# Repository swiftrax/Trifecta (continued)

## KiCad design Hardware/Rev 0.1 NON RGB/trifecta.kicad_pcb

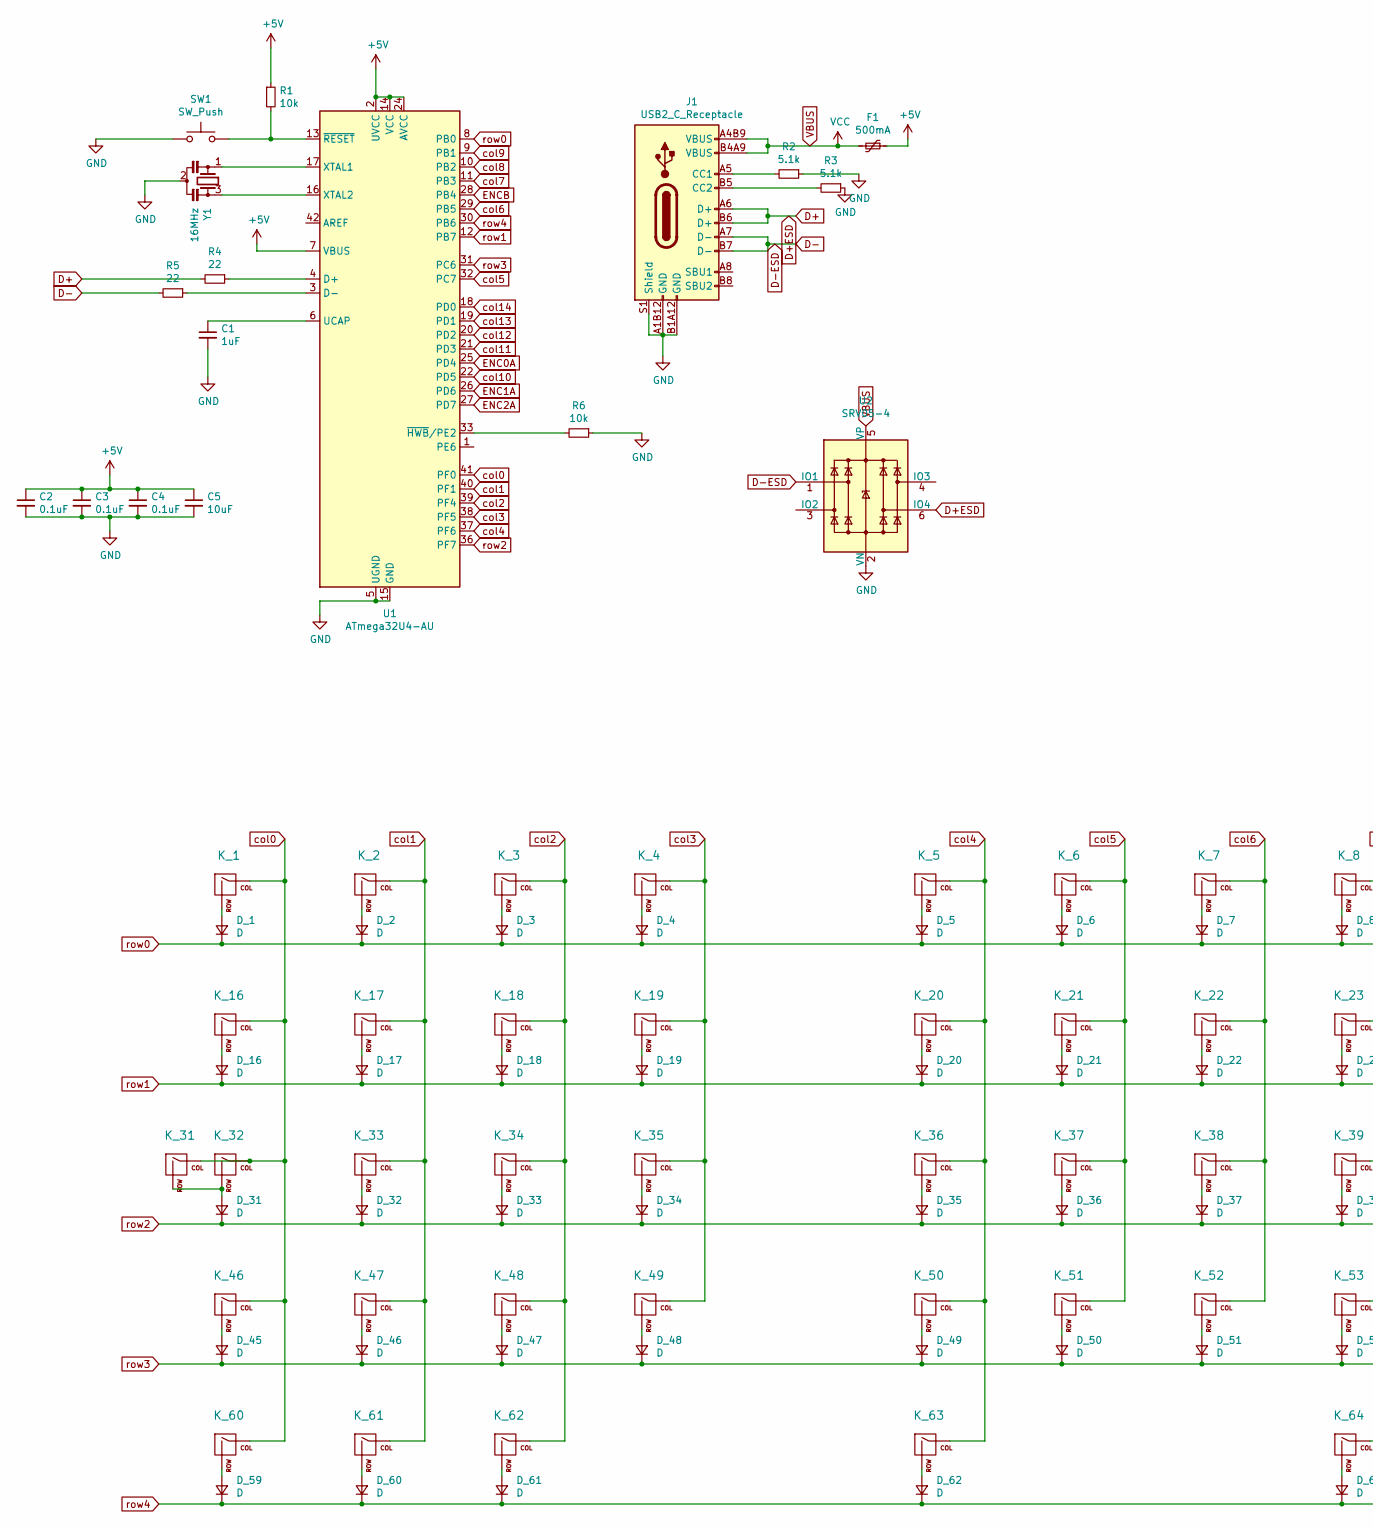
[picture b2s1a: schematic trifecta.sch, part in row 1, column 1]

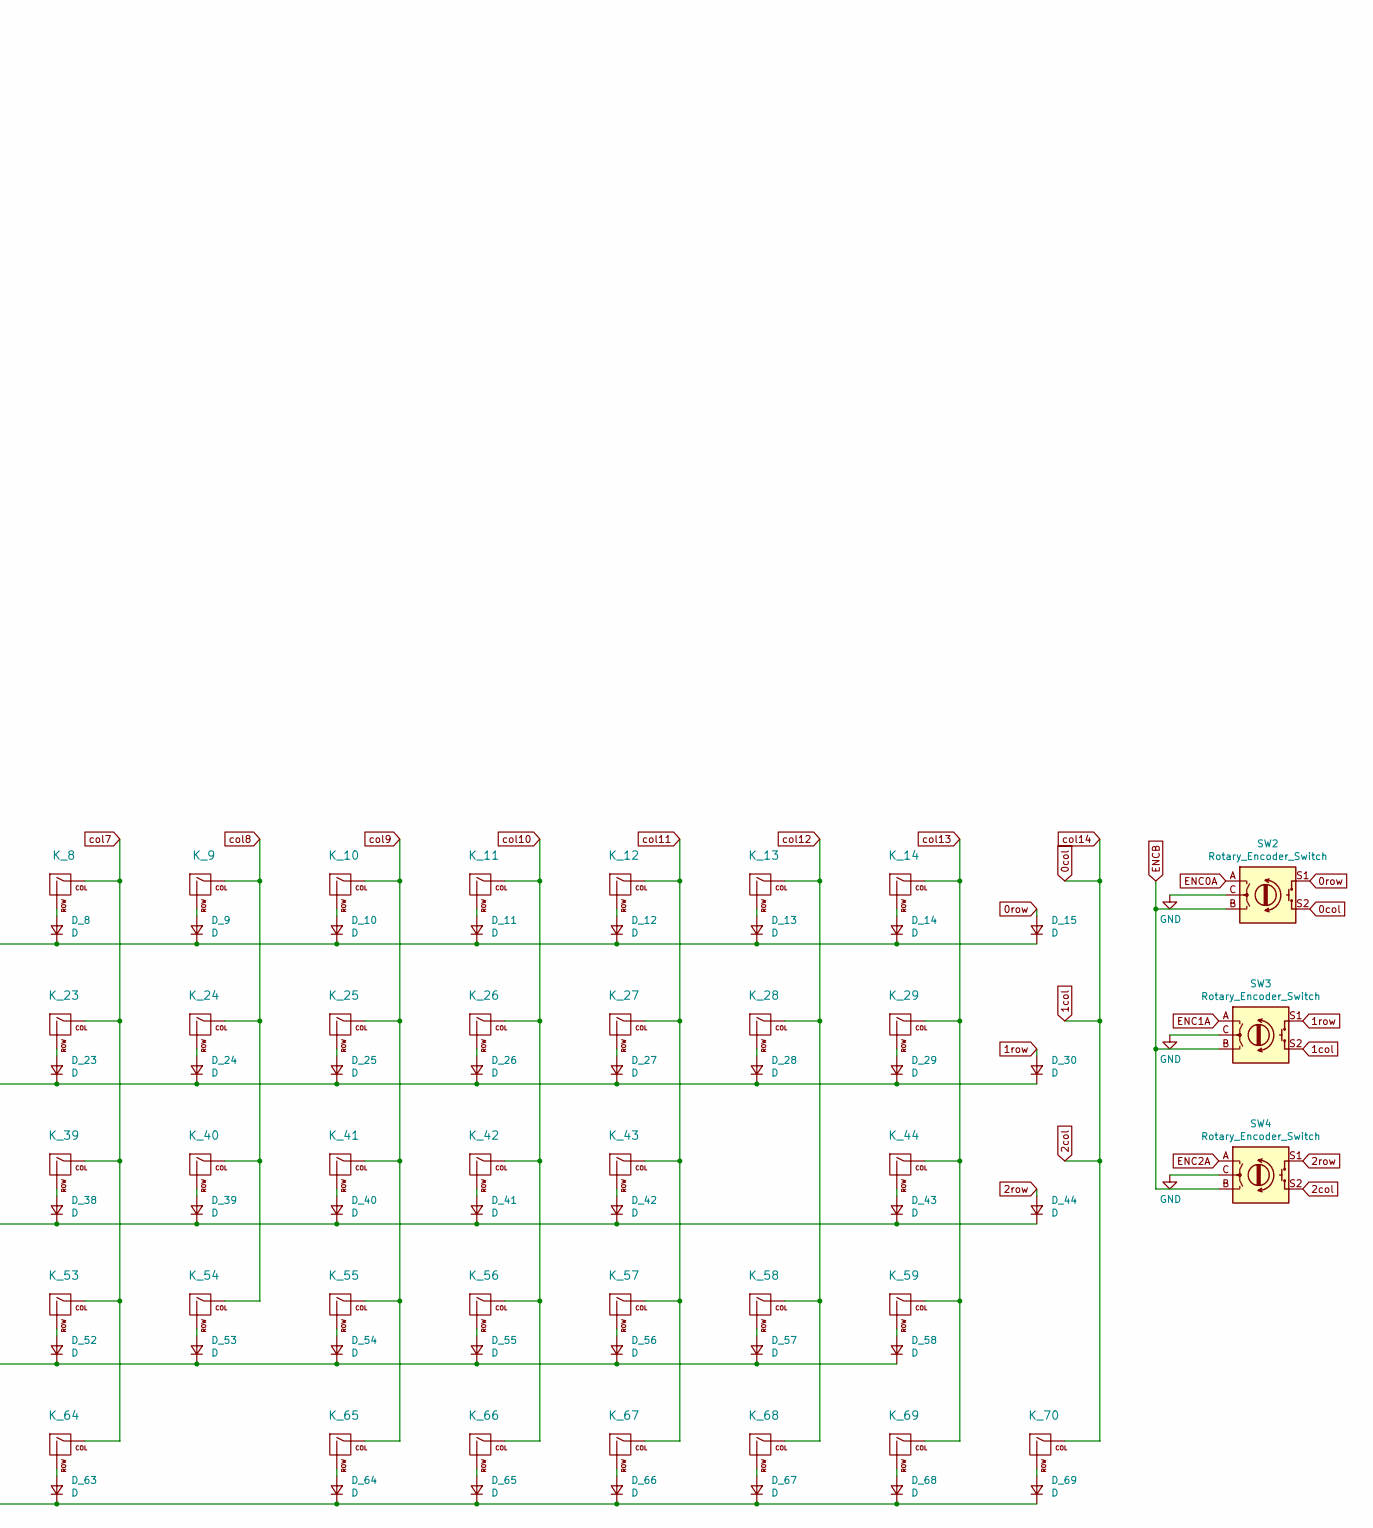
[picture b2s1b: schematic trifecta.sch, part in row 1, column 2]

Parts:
C1: 1uF; C_0805_2012Metric
C2, C3, C4: 0.1uF; C_0805_2012Metric
C5: 10uF; C_0805_2012Metric
D_1, D_2, D_3, D_4, D_5, D_6, D_7, D_8, D_9, D_10, D_11, D_12, D_13, D_14, D_15, D_16, D_17, D_18, D_19, D_20, D_21, D_22, D_23, D_24, D_25, D_26, D_27, D_28, D_29, D_30, D_31, D_32, D_33, D_34, D_35, D_36, D_37, D_38, D_39, D_40, D_41, D_42, D_43, D_44, D_45, D_46, D_47, D_48, D_49, D_50, D_51, D_52, D_53, D_54, D_55, D_56, D_57, D_58, D_59, D_60, D_61, D_62, D_63, D_64, D_65, D_66, D_67, D_68, D_69: D; D_SOD-123
F1: 500mA; Fuse_1206_3216Metric
J1: USB2_C_Receptacle; Mid_Mount-USB_C_HandSoldering
K_1, K_2, K_3, K_4, K_5, K_6, K_7, K_8, K_9, K_10, K_11, K_12, K_13, K_17, K_18, K_19, K_20, K_21, K_22, K_23, K_24, K_25, K_26, K_27, K_28, K_33, K_34, K_35, K_36, K_37, K_38, K_39, K_40, K_41, K_42, K_43, K_47, K_48, K_49, K_50, K_51, K_52, K_53, K_54, K_55, K_56, K_57, K_59, K_68, K_69, K_70: KEYSW; MXOnly-1U-NoLED
K_14: KEYSW; MXOnly-2U-ReversedStabilizers-NoLED
K_16, K_29: KEYSW; MXOnly-1.5U-NoLED
K_31, K_60, K_61, K_62, K_65, K_66, K_67: KEYSW; MXOnly-1.25U-NoLED
K_32, K_58: KEYSW; MXOnly-1.75U-NoLED
K_44, K_46, K_64: KEYSW; MXOnly-2.25U-ReversedStabilizers-NoLED
K_63: KEYSW; MXOnly-2.75U-ReversedStabilizers-NoLED
R1, R6: 10k; R_0805_2012Metric
R2, R3: 5.1k; R_0805_2012Metric
R4, R5: 22; R_0805_2012Metric
SW1: SW_Push; SKQG-1155865
SW2, SW3, SW4: Rotary_Encoder_Switch; RotaryEncoder_EC11
U1: ATmega32U4-AU; TQFP-44_10x10mm_P0.8mm
U2: SRV05-4; SOT-23-6
Y1: 16MHz; Resonator_SMD_muRata_CSTxExxV-3Pin_3.0x1.1mm_HandSoldering_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

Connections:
0col: K_70.1 (COL), SW2.S2, SW3.S2, SW4.S2, U1.18 (PD0)
0row: D_15.2 (A), SW2.S1
1row: D_30.2 (A), SW3.S1
2row: D_44.2 (A), SW4.S1
+5V: C2.1, C3.1, C4.1, C5.1, F1.1, R1.1, U1.2 (UVCC), U1.7 (VBUS), U1.14 (VCC), U1.24 (AVCC), U1.34 (VCC), U1.44 (AVCC)
D+: J1.A6 (D+), J1.B6 (D+), R4.2, U2.6 (IO4)
D-: J1.A7 (D-), J1.B7 (D-), R5.2, U2.1 (IO1)
ENC0A: SW2.A, U1.25 (PD4)
ENC1A: SW3.A, U1.26 (PD6)
ENC2A: SW4.A, U1.27 (PD7)
ENCB: SW2.B, SW3.B, SW4.B, U1.28 (PB4)
GND: C1.2, C2.2, C3.2, C4.2, C5.2, J1.A1B12 (GND), J1.B1A12 (GND), J1.S1 (Shield), R2.1, R3.1, R6.1, SW1.1, SW2.C, SW3.C, SW4.C, U1.5 (UGND), U1.15 (GND), U1.23 (GND), U1.35 (GND), U1.43 (GND), U2.2 (VN), Y1.2
unnamed: C1.1, U1.6 (UCAP)
unnamed: D_1.2 (A), K_1.2 (ROW)
unnamed: D_2.2 (A), K_2.2 (ROW)
unnamed: D_3.2 (A), K_3.2 (ROW)
unnamed: D_4.2 (A), K_4.2 (ROW)
unnamed: D_5.2 (A), K_5.2 (ROW)
unnamed: D_6.2 (A), K_6.2 (ROW)
unnamed: D_7.2 (A), K_7.2 (ROW)
unnamed: D_8.2 (A), K_8.2 (ROW)
unnamed: D_9.2 (A), K_9.2 (ROW)
unnamed: D_10.2 (A), K_10.2 (ROW)
unnamed: D_11.2 (A), K_11.2 (ROW)
unnamed: D_12.2 (A), K_12.2 (ROW)
unnamed: D_13.2 (A), K_13.2 (ROW)
unnamed: D_14.2 (A), K_14.2 (ROW)
unnamed: D_16.2 (A), K_16.2 (ROW)
unnamed: D_17.2 (A), K_17.2 (ROW)
unnamed: D_18.2 (A), K_18.2 (ROW)
unnamed: D_19.2 (A), K_19.2 (ROW)
unnamed: D_20.2 (A), K_20.2 (ROW)
unnamed: D_21.2 (A), K_21.2 (ROW)
unnamed: D_22.2 (A), K_22.2 (ROW)
unnamed: D_23.2 (A), K_23.2 (ROW)
unnamed: D_24.2 (A), K_24.2 (ROW)
unnamed: D_25.2 (A), K_25.2 (ROW)
unnamed: D_26.2 (A), K_26.2 (ROW)
unnamed: D_27.2 (A), K_27.2 (ROW)
unnamed: D_28.2 (A), K_28.2 (ROW)
unnamed: D_29.2 (A), K_29.2 (ROW)
unnamed: D_31.2 (A), K_31.2 (ROW), K_32.2 (ROW)
unnamed: D_32.2 (A), K_33.2 (ROW)
unnamed: D_33.2 (A), K_34.2 (ROW)
unnamed: D_34.2 (A), K_35.2 (ROW)
unnamed: D_35.2 (A), K_36.2 (ROW)
unnamed: D_36.2 (A), K_37.2 (ROW)
unnamed: D_37.2 (A), K_38.2 (ROW)
unnamed: D_38.2 (A), K_39.2 (ROW)
unnamed: D_39.2 (A), K_40.2 (ROW)
unnamed: D_40.2 (A), K_41.2 (ROW)
unnamed: D_41.2 (A), K_42.2 (ROW)
unnamed: D_42.2 (A), K_43.2 (ROW)
unnamed: D_43.2 (A), K_44.2 (ROW)
unnamed: D_45.2 (A), K_46.2 (ROW)
unnamed: D_46.2 (A), K_47.2 (ROW)
unnamed: D_47.2 (A), K_48.2 (ROW)
unnamed: D_48.2 (A), K_49.2 (ROW)
unnamed: D_49.2 (A), K_50.2 (ROW)
unnamed: D_50.2 (A), K_51.2 (ROW)
unnamed: D_51.2 (A), K_52.2 (ROW)
unnamed: D_52.2 (A), K_53.2 (ROW)
unnamed: D_53.2 (A), K_54.2 (ROW)
unnamed: D_54.2 (A), K_55.2 (ROW)
unnamed: D_55.2 (A), K_56.2 (ROW)
unnamed: D_56.2 (A), K_57.2 (ROW)
unnamed: D_57.2 (A), K_58.2 (ROW)
unnamed: D_58.2 (A), K_59.2 (ROW)
unnamed: D_59.2 (A), K_60.2 (ROW)
unnamed: D_60.2 (A), K_61.2 (ROW)
unnamed: D_61.2 (A), K_62.2 (ROW)
unnamed: D_62.2 (A), K_63.2 (ROW)
unnamed: D_63.2 (A), K_64.2 (ROW)
unnamed: D_64.2 (A), K_65.2 (ROW)
unnamed: D_65.2 (A), K_66.2 (ROW)
unnamed: D_66.2 (A), K_67.2 (ROW)
unnamed: D_67.2 (A), K_68.2 (ROW)
unnamed: D_68.2 (A), K_69.2 (ROW)
unnamed: D_69.2 (A), K_70.2 (ROW)
unnamed: J1.A5 (CC1), R2.2
unnamed: J1.B5 (CC2), R3.2
unnamed: R1.2, SW1.2, U1.13 (~RESET)
unnamed: R4.1, U1.4 (D+)
unnamed: R5.1, U1.3 (D-)
unnamed: R6.2, U1.33 (~HWB~/PE2)
unnamed: U1.16 (XTAL2), Y1.3
unnamed: U1.17 (XTAL1), Y1.1
VBUS: F1.2, J1.A4B9 (VBUS), J1.B4A9 (VBUS), U2.5 (VP)
col0: K_1.1 (COL), K_16.1 (COL), K_31.1 (COL), K_32.1 (COL), K_46.1 (COL), K_60.1 (COL), U1.41 (PF0)
col1: K_2.1 (COL), K_17.1 (COL), K_33.1 (COL), K_47.1 (COL), K_61.1 (COL), U1.40 (PF1)
col2: K_3.1 (COL), K_18.1 (COL), K_34.1 (COL), K_48.1 (COL), K_62.1 (COL), U1.39 (PF4)
col3: K_4.1 (COL), K_19.1 (COL), K_35.1 (COL), K_49.1 (COL), U1.38 (PF5)
col4: K_5.1 (COL), K_20.1 (COL), K_36.1 (COL), K_50.1 (COL), K_63.1 (COL), U1.37 (PF6)
col5: K_6.1 (COL), K_21.1 (COL), K_37.1 (COL), K_51.1 (COL), U1.32 (PC7)
col6: K_7.1 (COL), K_22.1 (COL), K_38.1 (COL), K_52.1 (COL), U1.29 (PB5)
col7: K_8.1 (COL), K_23.1 (COL), K_39.1 (COL), K_53.1 (COL), K_64.1 (COL), U1.11 (PB3)
col8: K_9.1 (COL), K_24.1 (COL), K_40.1 (COL), K_54.1 (COL), U1.10 (PB2)
col9: K_10.1 (COL), K_25.1 (COL), K_41.1 (COL), K_55.1 (COL), K_65.1 (COL), U1.9 (PB1)
col10: K_11.1 (COL), K_26.1 (COL), K_42.1 (COL), K_56.1 (COL), K_66.1 (COL), U1.22 (PD5)
col11: K_12.1 (COL), K_27.1 (COL), K_43.1 (COL), K_57.1 (COL), K_67.1 (COL), U1.21 (PD3)
col12: K_13.1 (COL), K_28.1 (COL), K_58.1 (COL), K_68.1 (COL), U1.20 (PD2)
col13: K_14.1 (COL), K_29.1 (COL), K_44.1 (COL), K_59.1 (COL), K_69.1 (COL), U1.19 (PD1)
row0: D_1.1 (K), D_2.1 (K), D_3.1 (K), D_4.1 (K), D_5.1 (K), D_6.1 (K), D_7.1 (K), D_8.1 (K), D_9.1 (K), D_10.1 (K), D_11.1 (K), D_12.1 (K), D_13.1 (K), D_14.1 (K), D_15.1 (K), U1.8 (PB0)
row1: D_16.1 (K), D_17.1 (K), D_18.1 (K), D_19.1 (K), D_20.1 (K), D_21.1 (K), D_22.1 (K), D_23.1 (K), D_24.1 (K), D_25.1 (K), D_26.1 (K), D_27.1 (K), D_28.1 (K), D_29.1 (K), D_30.1 (K), U1.12 (PB7)
row2: D_31.1 (K), D_32.1 (K), D_33.1 (K), D_34.1 (K), D_35.1 (K), D_36.1 (K), D_37.1 (K), D_38.1 (K), D_39.1 (K), D_40.1 (K), D_41.1 (K), D_42.1 (K), D_43.1 (K), D_44.1 (K), U1.36 (PF7)
row3: D_45.1 (K), D_46.1 (K), D_47.1 (K), D_48.1 (K), D_49.1 (K), D_50.1 (K), D_51.1 (K), D_52.1 (K), D_53.1 (K), D_54.1 (K), D_55.1 (K), D_56.1 (K), D_57.1 (K), D_58.1 (K), U1.31 (PC6)
row4: D_59.1 (K), D_60.1 (K), D_61.1 (K), D_62.1 (K), D_63.1 (K), D_64.1 (K), D_65.1 (K), D_66.1 (K), D_67.1 (K), D_68.1 (K), D_69.1 (K), U1.30 (PB6)

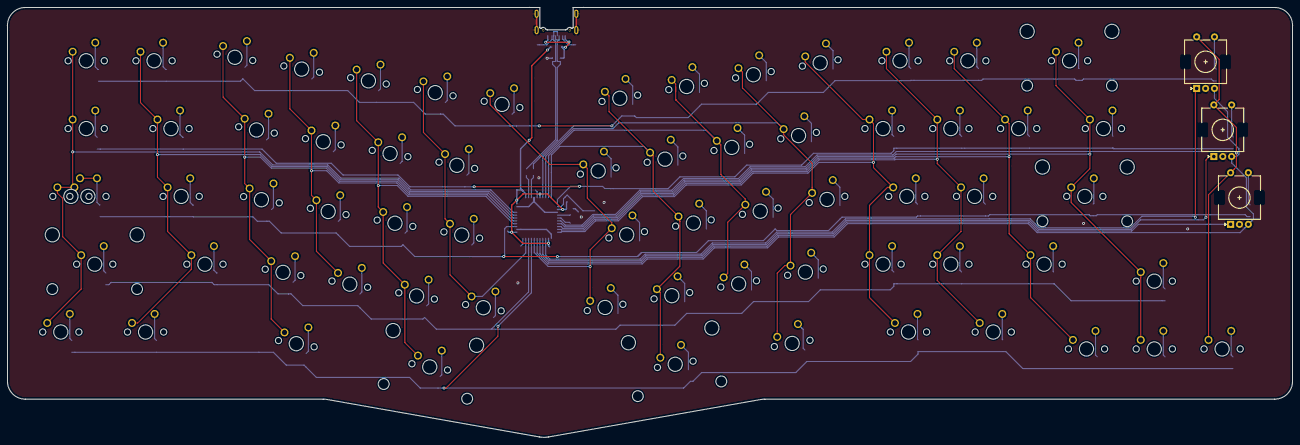
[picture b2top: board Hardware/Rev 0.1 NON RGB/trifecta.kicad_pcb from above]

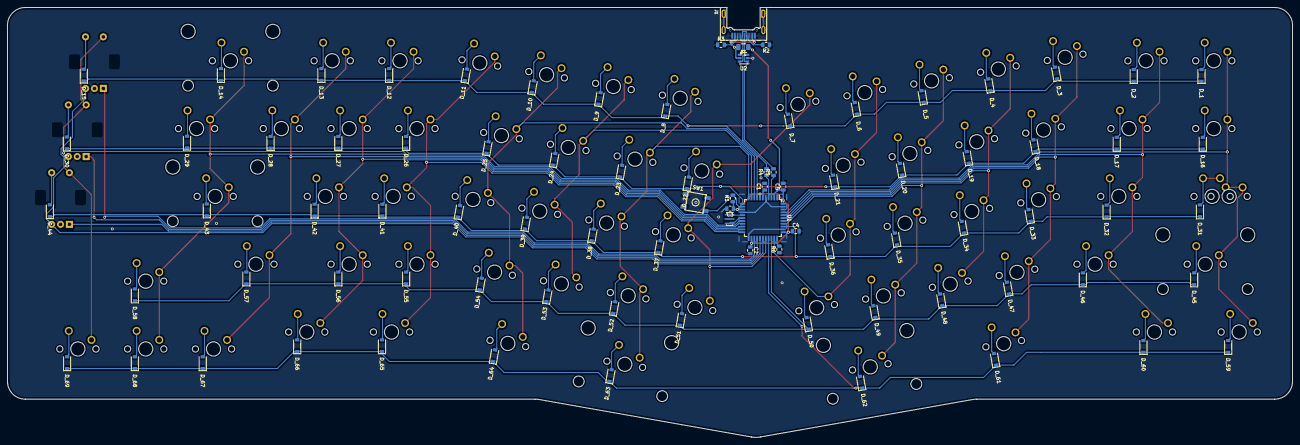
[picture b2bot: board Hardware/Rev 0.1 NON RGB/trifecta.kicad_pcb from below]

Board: 2 copper layers, 361.0 x 120.8 mm, 156 parts (86 on the bottom side), 107 nets.

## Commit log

2020-04-14 Remove Tracks
2020-04-14 Add Encoders
2020-04-14 Added PCB Edge Cuts
2020-04-14 Redo Edge Cuts
2020-04-14 Wire USB
2020-04-14 Wire Matrix + Place MCU
2020-04-15 Assign Rows + Cols to pins
2020-04-15 Place Traces for matrix + gnd fill
2020-04-16 Move Switches, remove tracks, add new layout drawing
2020-04-16 Wire switch Matrix together
2020-04-16 Wire MCU + GND fill
2020-04-17 Add Fusion Files
2020-04-17 Add new case
2020-04-18 Add new case design
    5mm top bezel
    Should be CNC ready
2020-04-19 Add Renders
2020-04-19 Add Stacked Acrylic case files
2020-04-20 Create LICENSE
2020-04-20 Reorganize
2020-04-20 Clean up files
2020-04-20 Add Top layer for encoder shaft
2020-04-21 Add more renders + Case step file
2020-05-06 Add New Case and Drawing
2020-05-07 Reorganize Files and add step files
2020-05-07 Add new case revision
2020-05-07 Enlarge encoder cutouts to allow it to be put in and out
2020-05-07 Change side edges of botom half
2020-05-07 Add more Renders
2020-05-07 Remove 5th rubber foot inlay + more renders
2020-05-07 Add RGB board + Move old design over
2020-05-08 Add homing bars to case + more renders
2020-05-09 Remove firmware
2020-05-09 Names of PCBs
2020-05-09 Update LICENSE
2020-05-09 Edit Case to have uniform bottom
2020-05-09 Edit top piece holes
2020-05-10 Add bottom logo
2020-05-10 New Renders, add bottom detail
2020-05-10 Edit Clearances and logo emboss
2020-05-11 Make Logo bigger
2020-05-11 Add Case .obj and .step
2020-05-12 Update Laser files for Rev 0.0 pcb
2020-05-12 Add Step of PCB
2020-05-21 PCB Final
2020-07-05 Add new laser cut DXF files
2020-07-05 Update Gerbers
2020-07-30 New Board
2020-08-03 03/08-1
2020-08-03 8/3/2020
2020-08-05 Clean up silkscreens, Add ground fill, Generate new gerbers
2020-08-05 Edit resistor silkscreen, Generate Gerbers
2020-08-06 LED Update
2020-08-06 Flip backspace stab regenerate gerbers
2020-08-07 08/07
2020-08-07 08/07 -2
2020-08-07 LED37
2020-08-07 8/7 Final
2020-08-07 Clean up silkscreen, tracks, and generate gerbers
2020-08-07 Fix more traces, regenerate gerbers
2020-08-07 Edit Silkscreens for HS version
    TODO: clean up tracks and add silkscreen art
2020-08-08 Add copper fill 0.5
2020-08-08 Revert "Edit Silkscreens for HS version"
    This reverts commit 5a8b713c0dac6e6c9a90fc558c8fc8e6b1fe5ec3.
2020-08-08 Clean up silkscreens, regenerate gerbers
2020-08-09 8/10
2020-08-11 8/11
2020-08-16 Fix silkscreen + generate gerbers
2020-08-17 move usb port out
2020-08-21 8/21
2020-08-21 8/21 -2
2020-08-21 8/21-3
2020-08-21 8/21 -4
2020-08-21 8/21-4
2020-09-06 RGB Matrix
2020-09-26 Edit images
2020-10-12 10/12
2020-10-13 10/13
2020-10-15 10/15
2020-10-15 10/16
2020-10-16 10/16-2
2020-10-16 10/16-3
2020-10-16 Trifecta Board
2020-10-16 Trifecta Keyboard
2020-10-18 Add case redesign
2020-10-18 10/18
2021-01-24 Rev0.6 Hotswap
2021-01-24 Degree Notation for PCBs
2021-01-24 Remove Edge Cuts
2021-01-24 Added folder for STM32 PCB
2021-01-24 cache
2021-02-07 2/8/2021
